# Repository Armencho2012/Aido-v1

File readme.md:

# AIDO — AI Study Assistant Robot

This repository contains the full AIDO project split across backend, frontend, firmware, tests, and 3D models.

## Repository structure

- `Aide server/` — backend voice API only, no browser UI.
- `Aide website/` — production-ready web application source and public assets.
- `Robot codes/` — MicroPython firmware and robot application logic.
- `Robot tests/` — hardware and software test scripts.
- `Robot 3d models/` — robot enclosure and part model files.

## Quick start

- Backend: run `Aide server` and configure `GROQ_API_KEY`.
- Frontend: build `Aide website` with `npm install` and `npm run build`.
- Robot firmware: deploy `Robot codes` to the Pico W device.
- Tests: run selected scripts from `Robot tests/harware` and `Robot tests/software`.

## Notes

- This repo is organized by subsystem, not by a single monolithic app.
- The backend service is API-only; the front-end and firmware are separate.
- Keep the `Aide website` folder clean from development-only artifacts.

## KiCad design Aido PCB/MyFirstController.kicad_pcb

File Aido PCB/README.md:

# Aido PCB

This folder contains the printed circuit board design files for the AIDO project.

## Files

- `MyFirstController.kicad_sch` — schematic design
- `MyFirstController.kicad_pcb` — PCB layout
- `MyFirstController.kicad_prl` — PCB rules file
- `MyFirstController.kicad_pro` — PCB project file
- `ERC.rpt` — electrical rules check report
- `images/` — board diagrams and reference images

## Notes

- Use KiCad to open and edit the PCB design files.
- Keep generated artifacts out of source control if you want the repository clean.

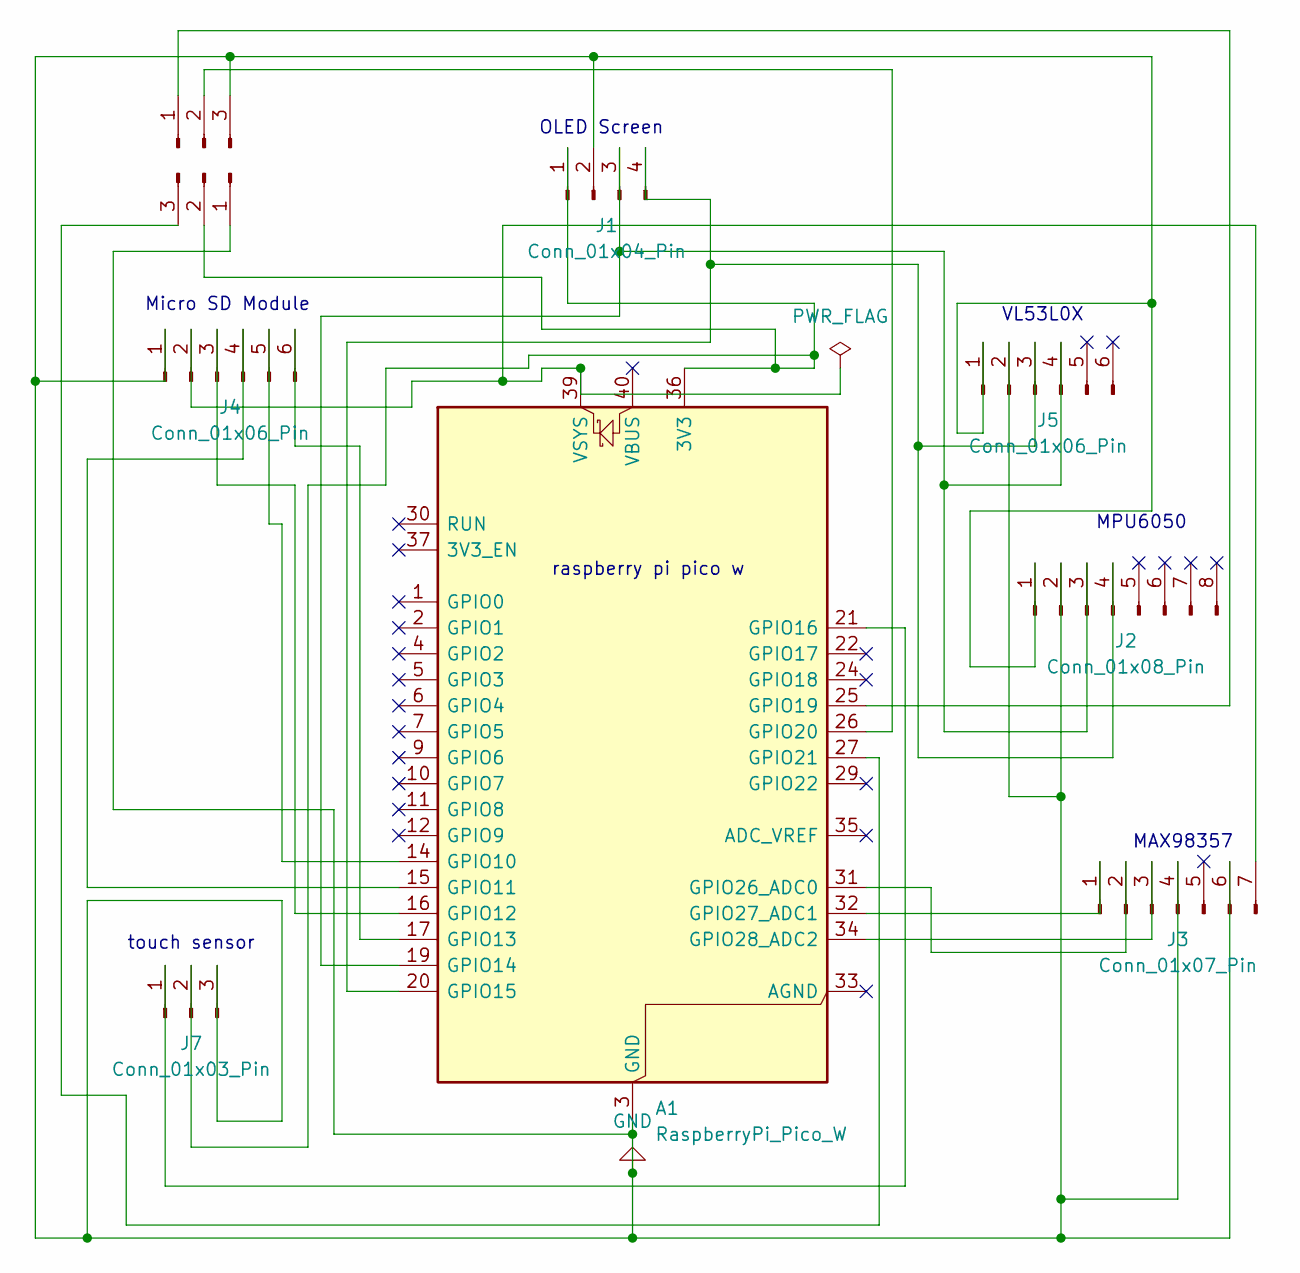
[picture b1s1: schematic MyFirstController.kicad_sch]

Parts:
A1: RaspberryPi_Pico_W; RaspberryPi_Pico_W_SMD_HandSolder
J1: Conn_01x04_Pin; PinSocket_1x04_P2.54mm_Vertical
J2: Conn_01x08_Pin; PinSocket_1x08_P2.54mm_Vertical
J3: Conn_01x07_Pin; PinSocket_1x07_P2.54mm_Vertical
J4, J5: Conn_01x06_Pin; PinSocket_1x06_P2.54mm_Vertical
J6, J7, J8: Conn_01x03_Pin; PinSocket_1x03_P2.54mm_Vertical

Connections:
GND: A1.3 (GND), A1.8 (GND), A1.13 (GND), A1.18 (GND), A1.23 (GND), A1.28 (GND), A1.38 (GND), J1.2, J2.1, J2.2, J3.4, J3.6, J4.1, J5.1, J5.2, J6.3, J7.3, J8.1
unnamed: A1.36 (3V3), J1.1, J7.2, J8.2
unnamed: A1.14 (GPIO10), J4.5
unnamed: A1.15 (GPIO11), J4.4
unnamed: A1.16 (GPIO12), J4.3
unnamed: A1.17 (GPIO13), J4.6
unnamed: A1.19 (GPIO14), J1.3, J2.3, J5.4
unnamed: A1.20 (GPIO15), J1.4, J2.4, J5.3
unnamed: A1.21 (GPIO16), J7.1
unnamed: A1.25 (GPIO19), J6.1
unnamed: A1.26 (GPIO20), J6.2
unnamed: A1.27 (GPIO21), J8.3
unnamed: A1.31 (GPIO26_ADC0), J3.2
unnamed: A1.32 (GPIO27_ADC1), J3.1
unnamed: A1.34 (GPIO28_ADC2), J3.3
unnamed: A1.39 (VSYS), J3.7, J4.2

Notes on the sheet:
raspberry pi pico w
MPU6050
Micro SD Module
MAX98357
touch sensor
OLED Screen
VL53L0X

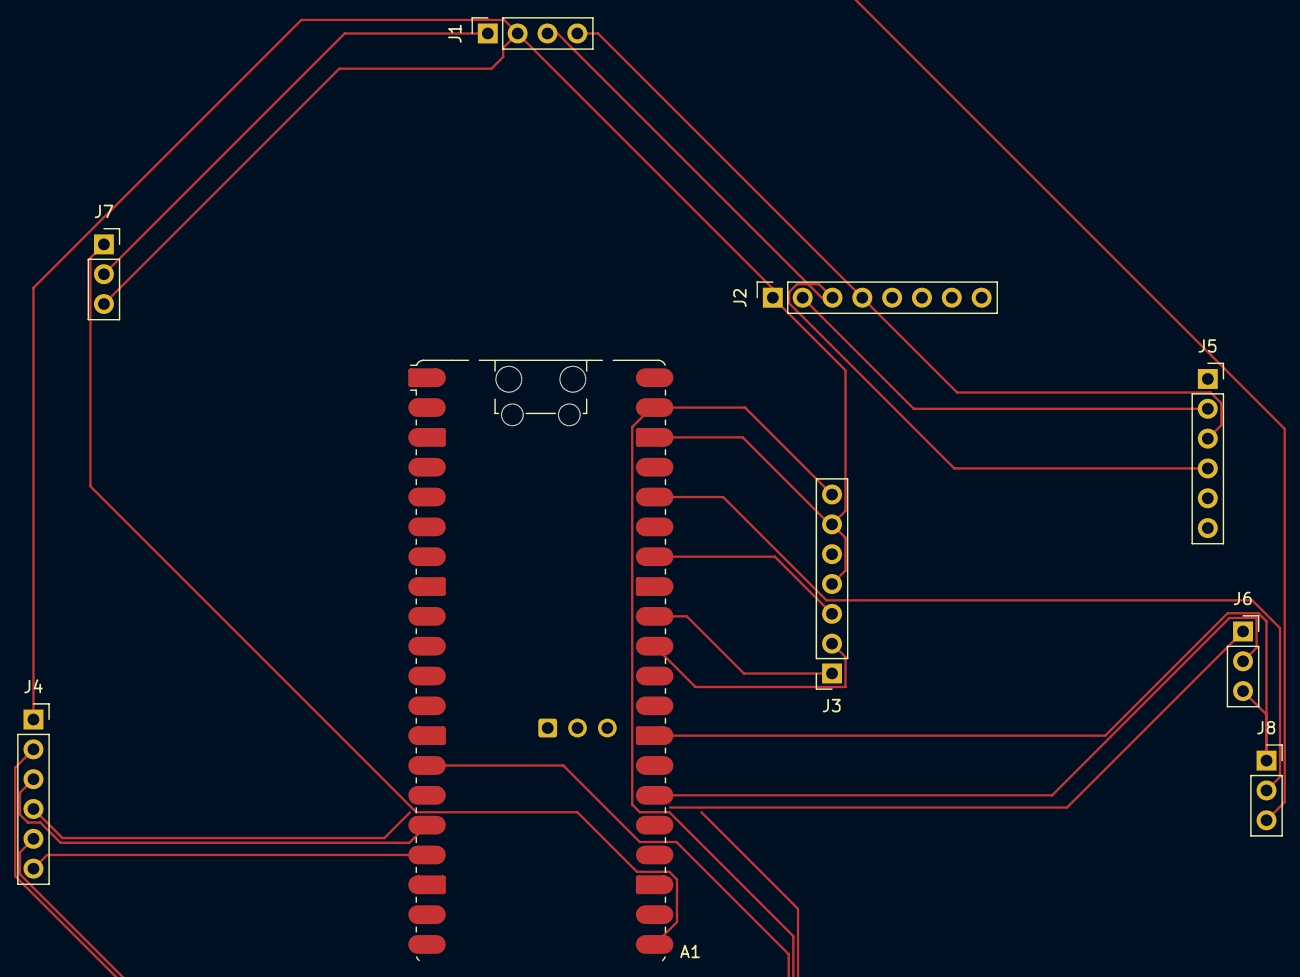
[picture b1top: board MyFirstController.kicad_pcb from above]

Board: 2 copper layers, 9 parts (0 on the bottom side), 16 nets.
